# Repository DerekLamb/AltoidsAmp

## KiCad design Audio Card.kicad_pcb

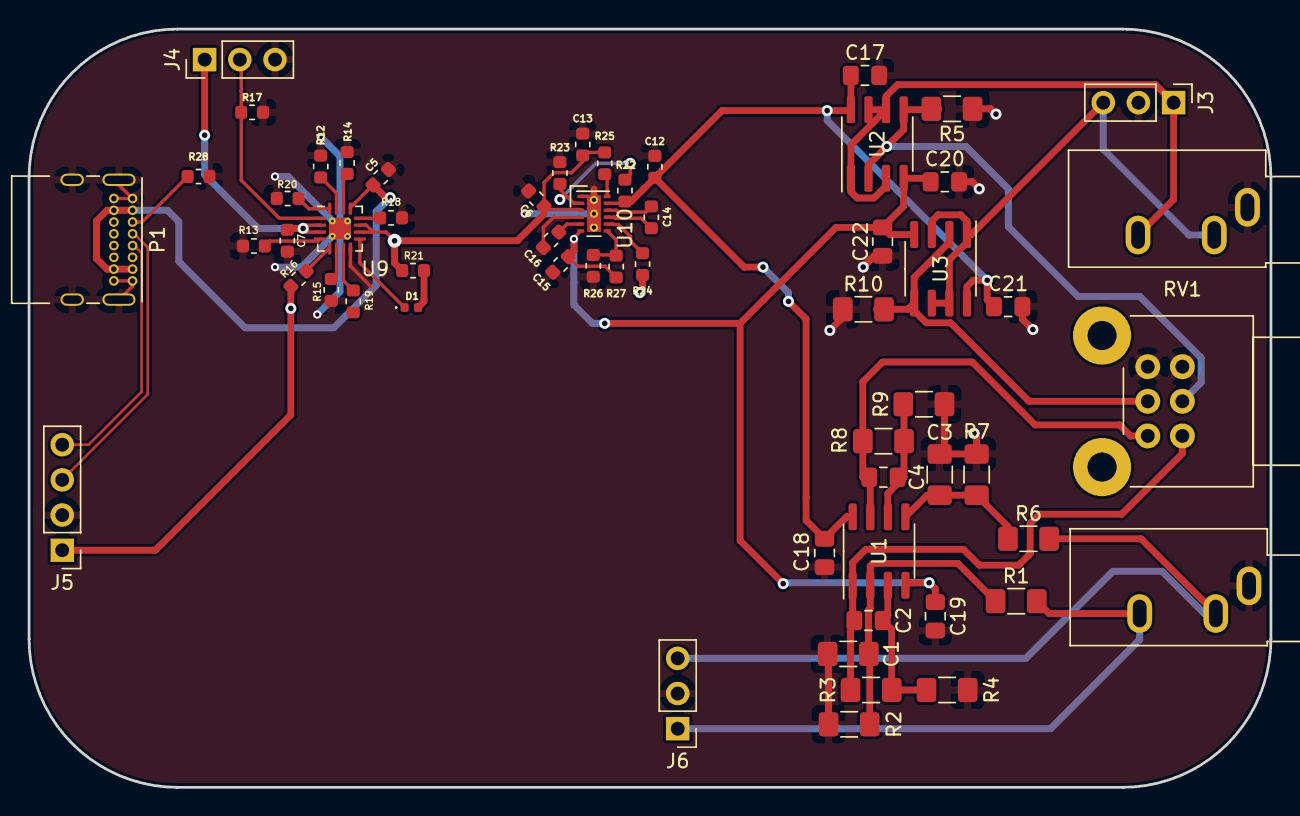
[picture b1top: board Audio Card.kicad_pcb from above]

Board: 2 copper layers, 89.7 x 54.8 mm, 59 parts (0 on the bottom side), 39 nets.

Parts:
C1, C3: 220 pF; C_1206_3216Metric_Pad1.42x1.75mm_HandSolder
C2, C4: 220pF; C_0805_2012Metric_Pad1.15x1.40mm_HandSolder
C5: 1uF; C_0603_1608Metric
C6, C7, C14, C16: 4.7uf; C_0603_1608Metric
C12, C13, C15: 2.2uF; C_0603_1608Metric
C17, C18, C19, C20, C21, C22: 88nF; C_0805_2012Metric_Pad1.15x1.40mm_HandSolder
D1: CHGLED; LED_0402_1005Metric
J1, J2: AudioJack3; Jack_3.5mm_CUI_SJ1-3533NG_Horizontal
J3, J4, J6: Conn_01x03_Male; PinHeader_1x03_P2.54mm_Vertical
J5: Conn_01x04_Male; PinHeader_1x04_P2.54mm_Vertical
P1: USB_C_Plug_USB2.0; USB_C_Receptacle_GCT_USB4085
R1, R5, R6, R10: R_US; R_1206_3216Metric_Pad1.42x1.75mm_HandSolder
R2, R7: 10k; R_1206_3216Metric_Pad1.42x1.75mm_HandSolder
R3, R8: 1.5k; R_1206_3216Metric_Pad1.42x1.75mm_HandSolder
R4, R9: 274ohm; R_1206_3216Metric_Pad1.42x1.75mm_HandSolder
R12, R13, R17, R24, R25: 10k; R_0603_1608Metric
R14, R15, R16, R19: 18k; R_0603_1608Metric
R18: 1.18k; R_0603_1608Metric
R20, R21: 1k; R_0603_1608Metric
R22, R27: 150k; R_0603_1608Metric
R23, R26: 180k; R_0603_1608Metric
R28: 56k; R_0603_1608Metric
RV1: R_POT_Dual_Separate; Potentiometer_Alps_RK09L_Double_Horizontal
U1, U2, U3: OPA1692; SOIC-8_3.9x4.9mm_P1.27mm
U9: BQ24075; VQFN-16-1EP_3x3mm_P0.5mm_EP1.6x1.6mm_ThermalVias
U10: LM27762; WSON-12-1EP_3x2mm_P0.5mm_EP1x2.65_ThermalVias

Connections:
+BATT: C7.1, J4.1, U9.2, U9.3
/Headphone amp/+2V: C12.1, C17.1, C18.1, C21.1, R22.2, U1.8, U2.8, U3.8, U10.11
/Headphone amp/-2V: C15.2, C19.1, C20.1, C22.1, R27.1, U1.4, U2.4, U3.4, U10.6
/Headphone amp/ampInL: J2.T, J6.3, R6.2
/Headphone amp/ampInR: J2.R, J6.1, R1.2
D+: J5.3, P1.A6
D-: J5.4, P1.A7
GND: C1.2, C3.2, C5.2, C6.2, C7.2, C12.2, C13.2, C15.1, C16.2, C17.2, C18.2, C19.2, C20.2, C21.2, C22.2, J1.S, J2.S, J3.2, J4.3, J5.2, J6.2, P1.A1, P1.A12, P1.B1, P1.B12, P1.S1, R2.1, R4.2, R5.1, R7.1, R9.2, R10.1, R12.2, R13.2, R14.2, R15.2, R17.1, R18.2, R20.2, R23.1, R26.2, R28.2, RV1.3, RV1.6, U9.8, U9.17, U10.1, U10.4, U10.13
NTC_Therm: J4.2, R17.2, U9.1
unnamed: C1.1, R1.1, R2.2, U1.2
unnamed: C2.1, R3.2, R4.1, U1.3
unnamed: C2.2, R3.1, RV1.1, U1.1
unnamed: C3.1, R6.1, R7.2, U1.5
unnamed: C4.1, R8.2, R9.1, U1.6
unnamed: C4.2, R8.1, RV1.4, U1.7
unnamed: C14.1, U10.10
unnamed: C14.2, U10.9
unnamed: C16.1, U10.5
unnamed: D1.1, U9.9
unnamed: D1.2, R21.2
unnamed: P1.A5, R28.1
unnamed: R5.2, RV1.2, U2.2, U2.5
unnamed: R10.2, RV1.5, U3.2, U3.5
unnamed: R12.1, U9.15
unnamed: R13.1, U9.4
unnamed: R14.1, U9.14
unnamed: R15.1, U9.6
unnamed: R16.1, U9.5
unnamed: R18.1, U9.12
unnamed: R19.2, U9.7
unnamed: R20.1, U9.16
unnamed: R22.1, R23.2, U10.2
unnamed: R24.2, U10.8
unnamed: R25.2, U10.12
unnamed: R26.1, R27.2, U10.7
VIN: C5.1, P1.A4, P1.A9, P1.B4, P1.B9, U9.13
VOUT: C6.1, C13.1, J5.1, R16.2, R21.1, R24.1, R25.1, U9.10, U9.11, U10.3
ampOutL: J1.T, J3.3, U3.1, U3.3, U3.6, U3.7
ampOutR: J1.R, J3.1, U2.1, U2.3, U2.6, U2.7

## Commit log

2023-07-18 Moving project to github
